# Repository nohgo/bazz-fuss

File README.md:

# Bazz Fuss Guitar Pedal

## Project Overview
This is a classic bazz fuss circuit modeled in LTSpice, built on a solderless breadboard, and designed in KiCad.

## Demo

## Technical Specifications
- 100k Ohm resistor
- 1N914 Diode
- 100k pot and knob
- 2N5088 / MPSA13 transistors
- 10uF capacitor
- 0.1uF capacitor
- 1/4" Mono Jack (output)
- 1/4" Stereo Jack (input)
- 9V battery
  
## How It works
It's easier to think of the circuit in two phases, when the transistor is on and when it's off. 
1. When the transistor is on the effect is obvious, everything on an equipotential with it is pulled to 0V. That creates the clipping at the bottom of the waveform.
2. When the transistor is off the diode is on (the voltage at the base is low), and the voltage difference across the diode pulls the input waveform up to around 1V.

The effects are best observed by plotting the waveform at the collector of the transistor, as the capacitor at the end removes the DC.

## Design and Validation Process

1. Simulation

I first simulated the circuit in LTSpice and observed the waveform while using the simulator to develop my conceptual understanding.

Circuit Schematic | Waveform Output
--------| --------
|

2. Physical Prototype

I then breadboarded the circuit (try out both transistors)

## KiCad Schematic
Finally, I took the design and designed a PCB for it in KiCad. I included the schematic, layout, and 3D model below.

3D Representation | Layout
--------| --------
 |

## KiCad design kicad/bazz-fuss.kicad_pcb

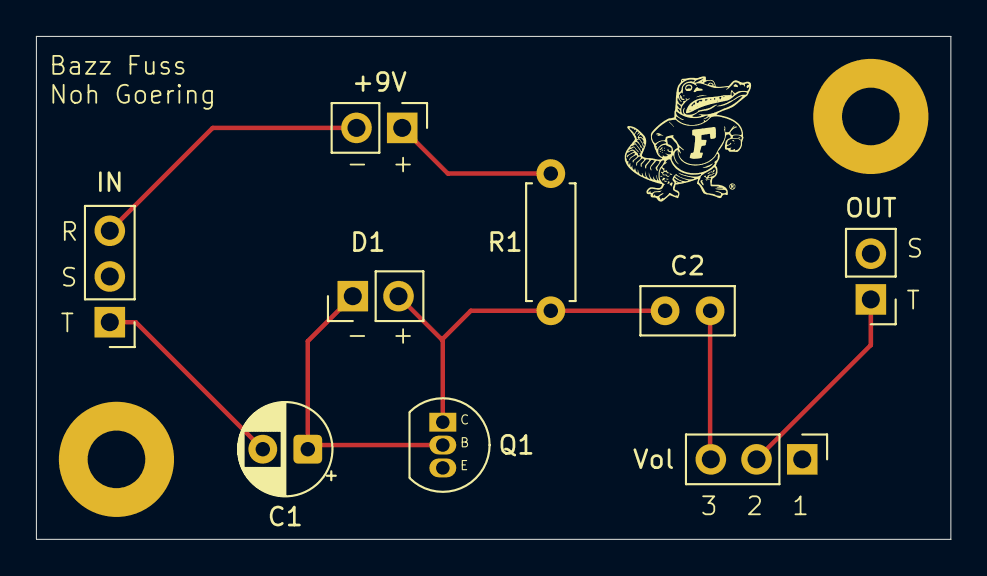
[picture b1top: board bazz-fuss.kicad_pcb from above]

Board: 2 copper layers, 50.8 x 27.9 mm, 9 parts (0 on the bottom side), 8 nets.

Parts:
+9V: Conn_01x02_Pin; PinHeader_1x02_P2.54mm_Vertical
C1: 4.7u; CP_Radial_D5.0mm_P2.50mm
C2: 0.1u; C_Disc_D5.0mm_W2.5mm_P2.50mm
D1: D; PinHeader_1x02_P2.54mm_Vertical
IN: Conn_01x03_Pin; PinHeader_1x03_P2.54mm_Vertical
OUT: Conn_01x02_Pin; PinHeader_1x02_P2.54mm_Vertical
Q1: NPN; TO-92_Inline
R1: 100k; R_Axial_DIN0207_L6.3mm_D2.5mm_P7.62mm_Horizontal
Vol: 100k; PinHeader_1x03_P2.54mm_Vertical

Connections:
/+9V: +9V.1, R1.2
/Ring: +9V.2, IN.3
/V_in: C1.2, IN.1
/V_out: OUT.1, Vol.2
GND: IN.2, OUT.2, Q1.3 (E), Vol.1
unnamed: C2.2, Vol.3
unnamed: C2.1, D1.2 (A), Q1.1 (C), R1.1
unnamed: C1.1, D1.1 (K), Q1.2 (B)

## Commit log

2025-08-21 make ltspice sim
2025-08-21 Create README.md and add basic desc
2025-08-21 Update README.md to properly size breadboard
2025-08-21 Fix broken image
2025-12-30 Build in KiCad
2025-12-30 Remove backups folder
2026-01-02 Update small README typo.
